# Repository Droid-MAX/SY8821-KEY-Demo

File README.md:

# SY8821-KEY-Demo
TPS-SY8821-KEY-Demo

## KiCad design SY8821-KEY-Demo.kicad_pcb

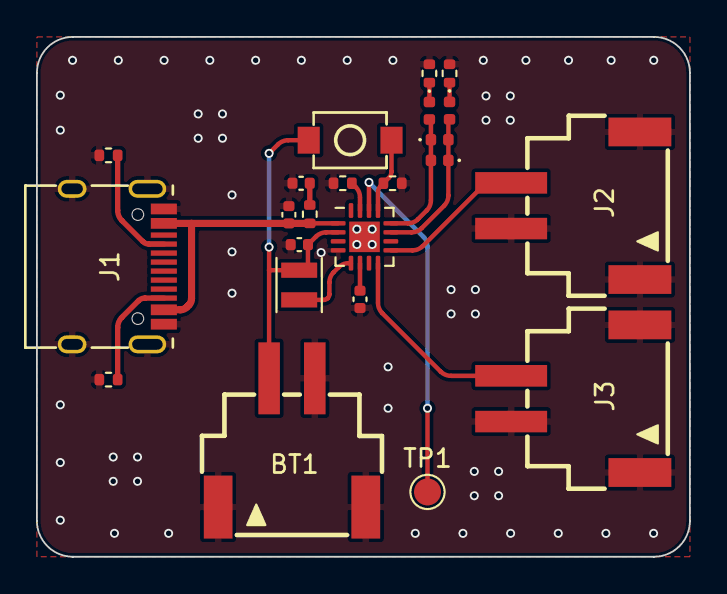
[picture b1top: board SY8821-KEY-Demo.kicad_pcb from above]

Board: 2 copper layers, 36.3 x 28.9 mm, 23 parts (0 on the bottom side), 17 nets.

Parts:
BT1: Battery_Cell; CONN-SMD_2.54-2PWT
C1, C2: 1uF; C_0402_1005Metric
C3, C4: 10uF; C_0402_1005Metric
D1, D2, D3, D4: LED_0402_1005Metric
J1: USB_C_Receptacle_USB2.0; USB-C_16Pin
J2, J3: Conn_01x02_Pin; CONN-SMD_2.54-2PWT
L1: 2.2uH; L_Sunlord_SWPA252012S
R1, R2: 5.1K; R_0402_1005Metric
R3: 1Ω; R_0402_1005Metric
R4: 2K; R_0402_1005Metric
R5: 10K; R_0402_1005Metric
R6, R7: 100Ω; R_0402_1005Metric
SW1: SW_Push; SW-SMD_L3.9-W2.9-LS4.8
TP1: NTC; TestPoint_Pad_D1.5mm
U1: SY8821; LQFN-16-1EP_3x3mm_P0.5mm_EP1.7x1.7mm

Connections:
GND: BT1.2 (-), BT1.3, BT1.4, C1.2, C2.2, C3.2, C4.2, J1.A1 (GND), J1.B1 (GND), J1.S1 (SHIELD), J2.1, J2.3, J2.4, J3.1, J3.3, J3.4, R1.2, R2.2, R4.1, R5.2, R6.2, R7.2, U1.4 (GND), U1.17 (GND)
unnamed: BT1.1 (+), C3.1, L1.1, SW1.2, U1.2 (BAT)
unnamed: C1.1, R3.2
unnamed: D1.2 (A), D2.1 (K), D3.2 (A), U1.11 (LED2)
unnamed: D1.1 (K), D2.2 (A), D4.2 (A), U1.12 (LED1)
unnamed: D3.1 (K), R6.1
unnamed: D4.1 (K), R7.1
unnamed: J1.A5 (CC1), R1.1
unnamed: J1.B5 (CC2), R2.1
unnamed: J2.2, U1.9 (VOR)
unnamed: J3.2, U1.8 (VOL)
unnamed: R4.2, U1.15 (ICH)
unnamed: R5.1, SW1.1, U1.13 (KEY)
unnamed: L1.2, U1.5 (LX)
unnamed: TP1.1, U1.14 (NTC)
unnamed: C4.1, U1.6 (VSYS)
VCC: C2.1, J1.A4 (VBUS), J1.B4 (VBUS), R3.1, U1.1 (VIN)

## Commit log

2023-11-26 init commit
